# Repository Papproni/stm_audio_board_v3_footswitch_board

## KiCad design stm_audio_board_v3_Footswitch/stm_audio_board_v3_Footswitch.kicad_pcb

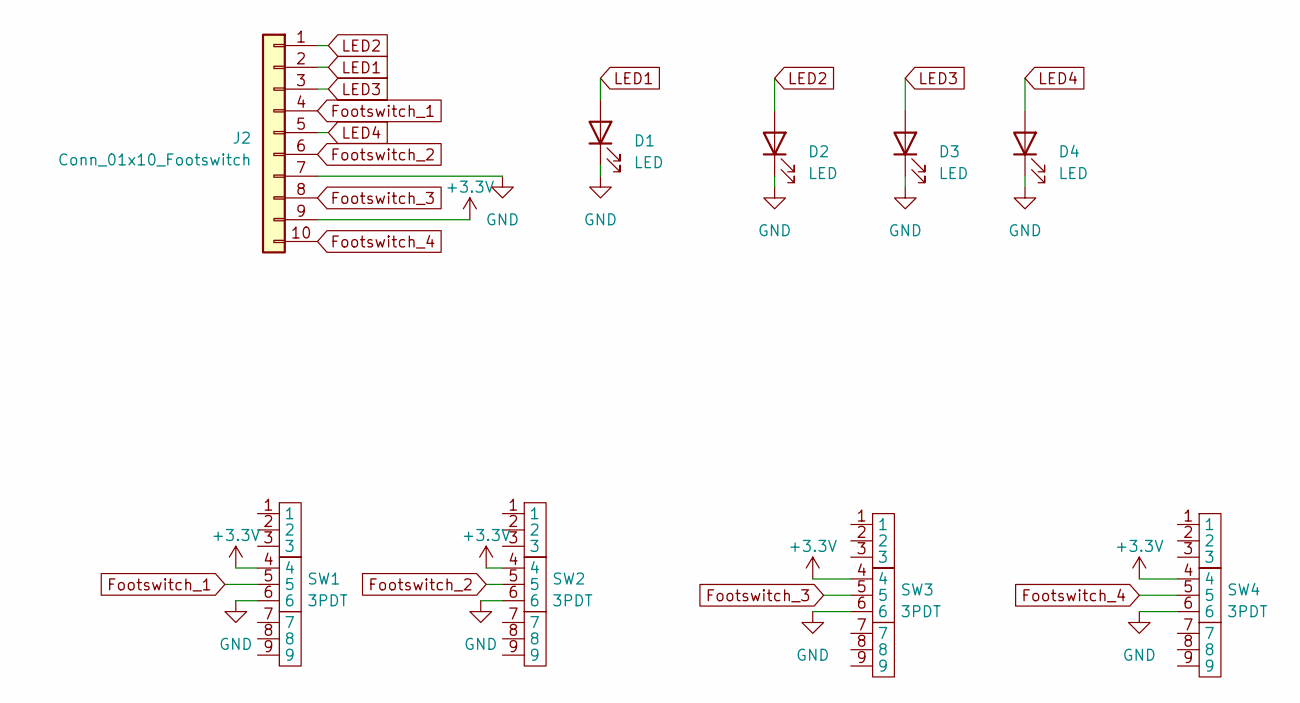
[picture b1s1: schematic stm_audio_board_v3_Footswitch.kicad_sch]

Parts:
D1, D2, D3, D4: LED; LED_D5.0mm
J2: Conn_01x10_Footswitch; IDC-Header_2x05_P2.54mm_Vertical; LCSC Part C5665
SW1, SW2, SW3, SW4: 3PDT

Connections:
+3.3V: J2.9, SW1.4, SW2.4, SW3.4, SW4.4
Footswitch_1: J2.4, SW1.5
Footswitch_2: J2.6, SW2.5
Footswitch_3: J2.8, SW3.5
Footswitch_4: J2.10, SW4.5
GND: D1.1 (K), D2.1 (K), D3.1 (K), D4.1 (K), J2.7, SW1.6, SW2.6, SW3.6, SW4.6
LED1: D1.2 (A), J2.2
LED2: D2.2 (A), J2.1
LED3: D3.2 (A), J2.3
LED4: D4.2 (A), J2.5

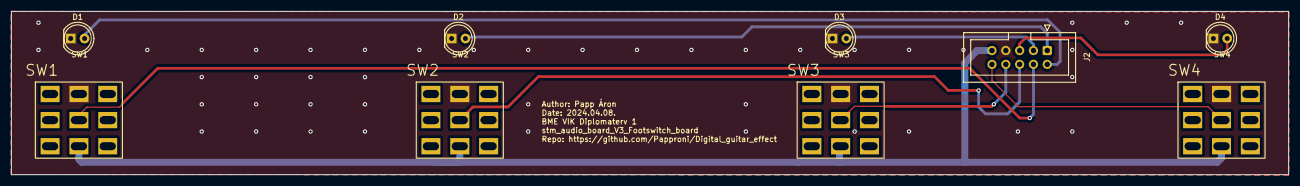
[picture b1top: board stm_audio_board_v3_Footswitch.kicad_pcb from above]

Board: 2 copper layers, 234.7 x 30.0 mm, 9 parts (0 on the bottom side), 10 nets.

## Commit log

2024-04-06 3pdt switch symbol created, basic board layout created
2024-04-06 Problem with new footprint grid and pin assignements
2024-04-07 updated symbol for 3pdt, created connections
2024-04-07 gerber added
2024-04-08 footswitches are now 70mm apart
